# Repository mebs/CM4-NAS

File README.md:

# CM4 NAS Board [UNMAINTAINED]

This Compute Module 4 carrier board design exposes a subset of the CM4's interfaces, including its single PCIe 2.0 lane to accept an external SATA controller card.
This design is based off of the official Raspberry Pi Foundation's CM4 IO board (the KiCad project is available on the [IO board official page](https://www.raspberrypi.org/products/compute-module-4-io-board/?resellerType=home)). Removed the IO that was less relevant for a NAS and rearranged the remaining interfaces for a smaller footprint that would fit within the width of a standard 3.5" hard drive.

The board was intentionally kept simple to limit mistakes as this is my first ever attempt at designing a PCB and I have no background in electronics, so all the power management is left to external power supplies and buck converters. It's important to use good quality regulated power supplies with this board as it offers no protection other than what is built into the CM4.

Also made 3D printed enclosure for the final product. Design available here: https://www.thingiverse.com/thing:4820662

Feel free to explore the discussion section of this repo to share ideas.

[Latest Reddit post here.](https://www.reddit.com/r/raspberry_pi/comments/mkbxss/cm4_custom_nas_complete/)

##### Table of Contents
- [Software](#software)
- [Board IO](#board-io)
  * [CM4 IO Breakout](#cm4-io-breakout)
  * [Other Connections on the Board](#other-connections-on-the-board)
- [PCB Assembly](#pcb-assembly)
  * [Manufacturing](#manufacturing)
  * [Required Parts](#required-parts)
  * [Building](#building)
- [Pinout](#pinout)
- [Revision History](#revision-history)

# Software
For the software part of this project, I highly recommend [Jeff Geerling's repo](https://github.com/geerlingguy/raspberry-pi-pcie-devices/issues), where he documented similar endeavors, but you will likely have to recompile the kernel after enabling some modules to be able to use a PCIe SATA controller.

Don't hesitate to ask questions in the Discussion tab of this repo.

# Board IO
## CM4 IO Breakout
The interfaces the board forwards from the CM4 are the following:
- **PCIe x1 Gen2**: Good old PCIe 2.0, nothing special about it... if not that it's on a Raspberry Pi.
- **Ethernet**: To reduce the number of components on the board and make assembly easier, a MagJack is used instead of a simple RJ45 connector. I had to look this up when I saw it in the IO board design, but a MagJack seems to be simply an RJ45 connector with integrated filters to help with signal integrity. Footprint is specific to the part listed bellow.
- **Single master/slave USB, selected with jumper**: A USB type A port to plug a keyboard, a flash drive, a hub, or whatever you want to use as a USB slave to the CM4. Footprint is not standard so make sure it fits yours if you manufacture the PCB. Can also be used in slave mode (CM4 as slave). You would use this to program the eMMC with you computer. This connection taps into the same single USB bus the CM4 has to offer, but when this is used, the VCC input from the master signals that the CM4 should behave as a slave. Currently the footprint for this is a simple 5 pin header.
- **Full size HDMI**:  Mostly for debugging purposes, hooked to the HDMI0 output of the CM4.
- **I²C**: This is marked "OLED" on the board because this was the intended use, but you can use this to slave any I²C device to the CM4. Five-pin JST connector footprint (fits simple headers too).
- **Single wire temperature sensor**: Marked "Temp_sensor" on the board, hooked to GPIO_4 on the CM4. I would recommend using it for a temp sensor near the SATA controller because they can get really hot and control the fan (see bellow) based on that.
- **9 GPIOs**: General purpose IO header, including Gnd, 3V3 and 5V pins.
- **Configuration headers**: nRPIBOOT, EEPROM_nWP, AIN1, SYNC_IN, SYNC_OUT, TV_OUT, GLOBAL_EN, RUN_PG, WL_nDis, BT_nDis. The pinout is detailed on the board.

## Other Connections on the Board
Other than relaying the compute module's IOs, the board adds other connections, mainly for power.
- **Fan control**: The board expects a dedicated PWM fan controller IC (see part list). Its output is routed to this JST connector (or your typical PWM fan connector) marked "Fan_PWM" on the board.
- **USB selection headers**: To avoid needing a USB MUX on board, this header should be used with a jumper to select if you want to use the USB bus as master or as slave.
- **Power input**: The board expects a 5V input for the CM4, and a 12V input for the PCIe card, both through the same JST connector labeled "PWR_IN".
- **3V3 buck**: The PCIe card also requires a dedicated 3V3 supply. This can be provided through the "3V3_BUCK" header near the power input. The pinout was made to accommodate [this daughter board](https://www.aliexpress.com/item/32817933017.html?spm=a2g0s.9042311.0.0.27424c4dr779wi) from AliExpress, but you can use whatever you want for as long as you follow the pinout bellow.
- **HDDs power**: Labeled "SATA_PWR". This is the power rail for the hard drives.

# PCB Assembly
## Manufacturing
There is a *Fab* folder at the repo's root. This folder contains all the files that you need to order PCBs from a manufacturer. You will find in the folder a Fab_rev1.4.zip archive that is all you need to order from JLC PCB. This is the latest version and the one I have been running for months now.

## Required Parts
Other than the standard caps and resistors, here are the components you will need if you want to assemble the board:
- **High density connectors** ([digikey](https://www.digikey.ca/en/products/detail/hirose-electric-co-ltd/DF40C-100DS-0.4V%2851%29/1969495), [LCSC](https://lcsc.com/product-detail/Mezzanine-Connectors-Board-to-Board_HRS-Hirose-DF40C-100DS-0-4V-51_C597931.html)): You will need these to connect the CM4 to the board. They can be very daunting, but I found [this video](https://www.youtube.com/watch?v=eukcrFc18P4) of someone neatly soldering them with a hot air gun. When I finaly got to try it, I was surprise at how doable it was.
- **MagJack** ([digikey](https://www.digikey.ca/en/products/detail/bel-fuse-inc/0826-1G1T-43-F/2107992)): I made the footprint for this specific one. It's expensive and I should have looked on LCSC before ordering.
- **Fan controller** ([digikey](https://www.digikey.ca/en/products/detail/microchip-technology/EMC2301-1-ACZL-TR/4696431), [LCSC](https://lcsc.com/product-detail/_MICROCHIP_EMC2301-1-ACZL-TR_EMC2301-1-ACZL-TR_C148036.html)): This chip is the exact same one that is on the official IO board and it's controlled by the CM4 through I²C.
- **ESD sinks** ([digikey](https://www.digikey.ca/en/products/detail/texas-instruments/TPD4EUSB30DQAR/2503671), [LCSC](https://lcsc.com/product-detail/Diodes-ESD_Texas-Instruments-TPD4EUSB30DQAR_C90627.html)): They are optional in my (very uninformed) opinion. I think they were included on the IO board for POE applications mostly.
- **Signal buffer** ([digikey](https://www.digikey.ca/en/products/detail/diodes-incorporated/74LVC1G07SE-7/2356550), [LCSC](https://lcsc.com/product-detail/Logic-Buffers-Drivers-Receivers-Transceivers_Diodes-Incorporated-74LVC1G07SE-7_C67531.html)): Used for the power LED and to buffer RUN_PG signal to be able to wake the CM4 from a sleep state.
- **HDMI connector** ([LCSC](https://lcsc.com/product-detail/Audio-Video-Connectors_SOFNG-HDMI-019S_C111617.html)): Basic full size HDMI connector.

## Building
To build the board, you will need a soldering iron and a hot air gun (or a reflow oven). I would recommend starting with the Hirose high density connectors as they are without a doubt the hardest part. [This video](https://www.youtube.com/watch?v=eukcrFc18P4) I referred to earlier is a good starting point, it makes for a fine tutorial.
It only took a couple tries before I could get a decent result (image from microscope at around 50-60x):

Once the HD connectors are in place, you can move on to the ESD sinks. They are very small and can also be daunting, but soldering them turned out to be easier than expected.
The trick is to put as little solder paste as possible and the chips will naturally be pulled in place by the solder's surface tension.

The rest of the parts should be fairly easy to solder with a standard iron.

# Pinout

# Revision History
- **1**: Initial version
- **1.1**: Fixed wrong footprint for fan controller
- **1.2**: Changed the USB select headers for a simpler solution with a single jumper
- **1.3**: Replaced the HDMI header by a full size HDMI female connector, exposed 9 GPIOs, inverted polarity back for PCIe Tx/Rx signals and added a power LED.
- **1.4**: Add pin to OLED connector for button, use SMD caps and LEDs, more info on silkscreen and fixed some traces.

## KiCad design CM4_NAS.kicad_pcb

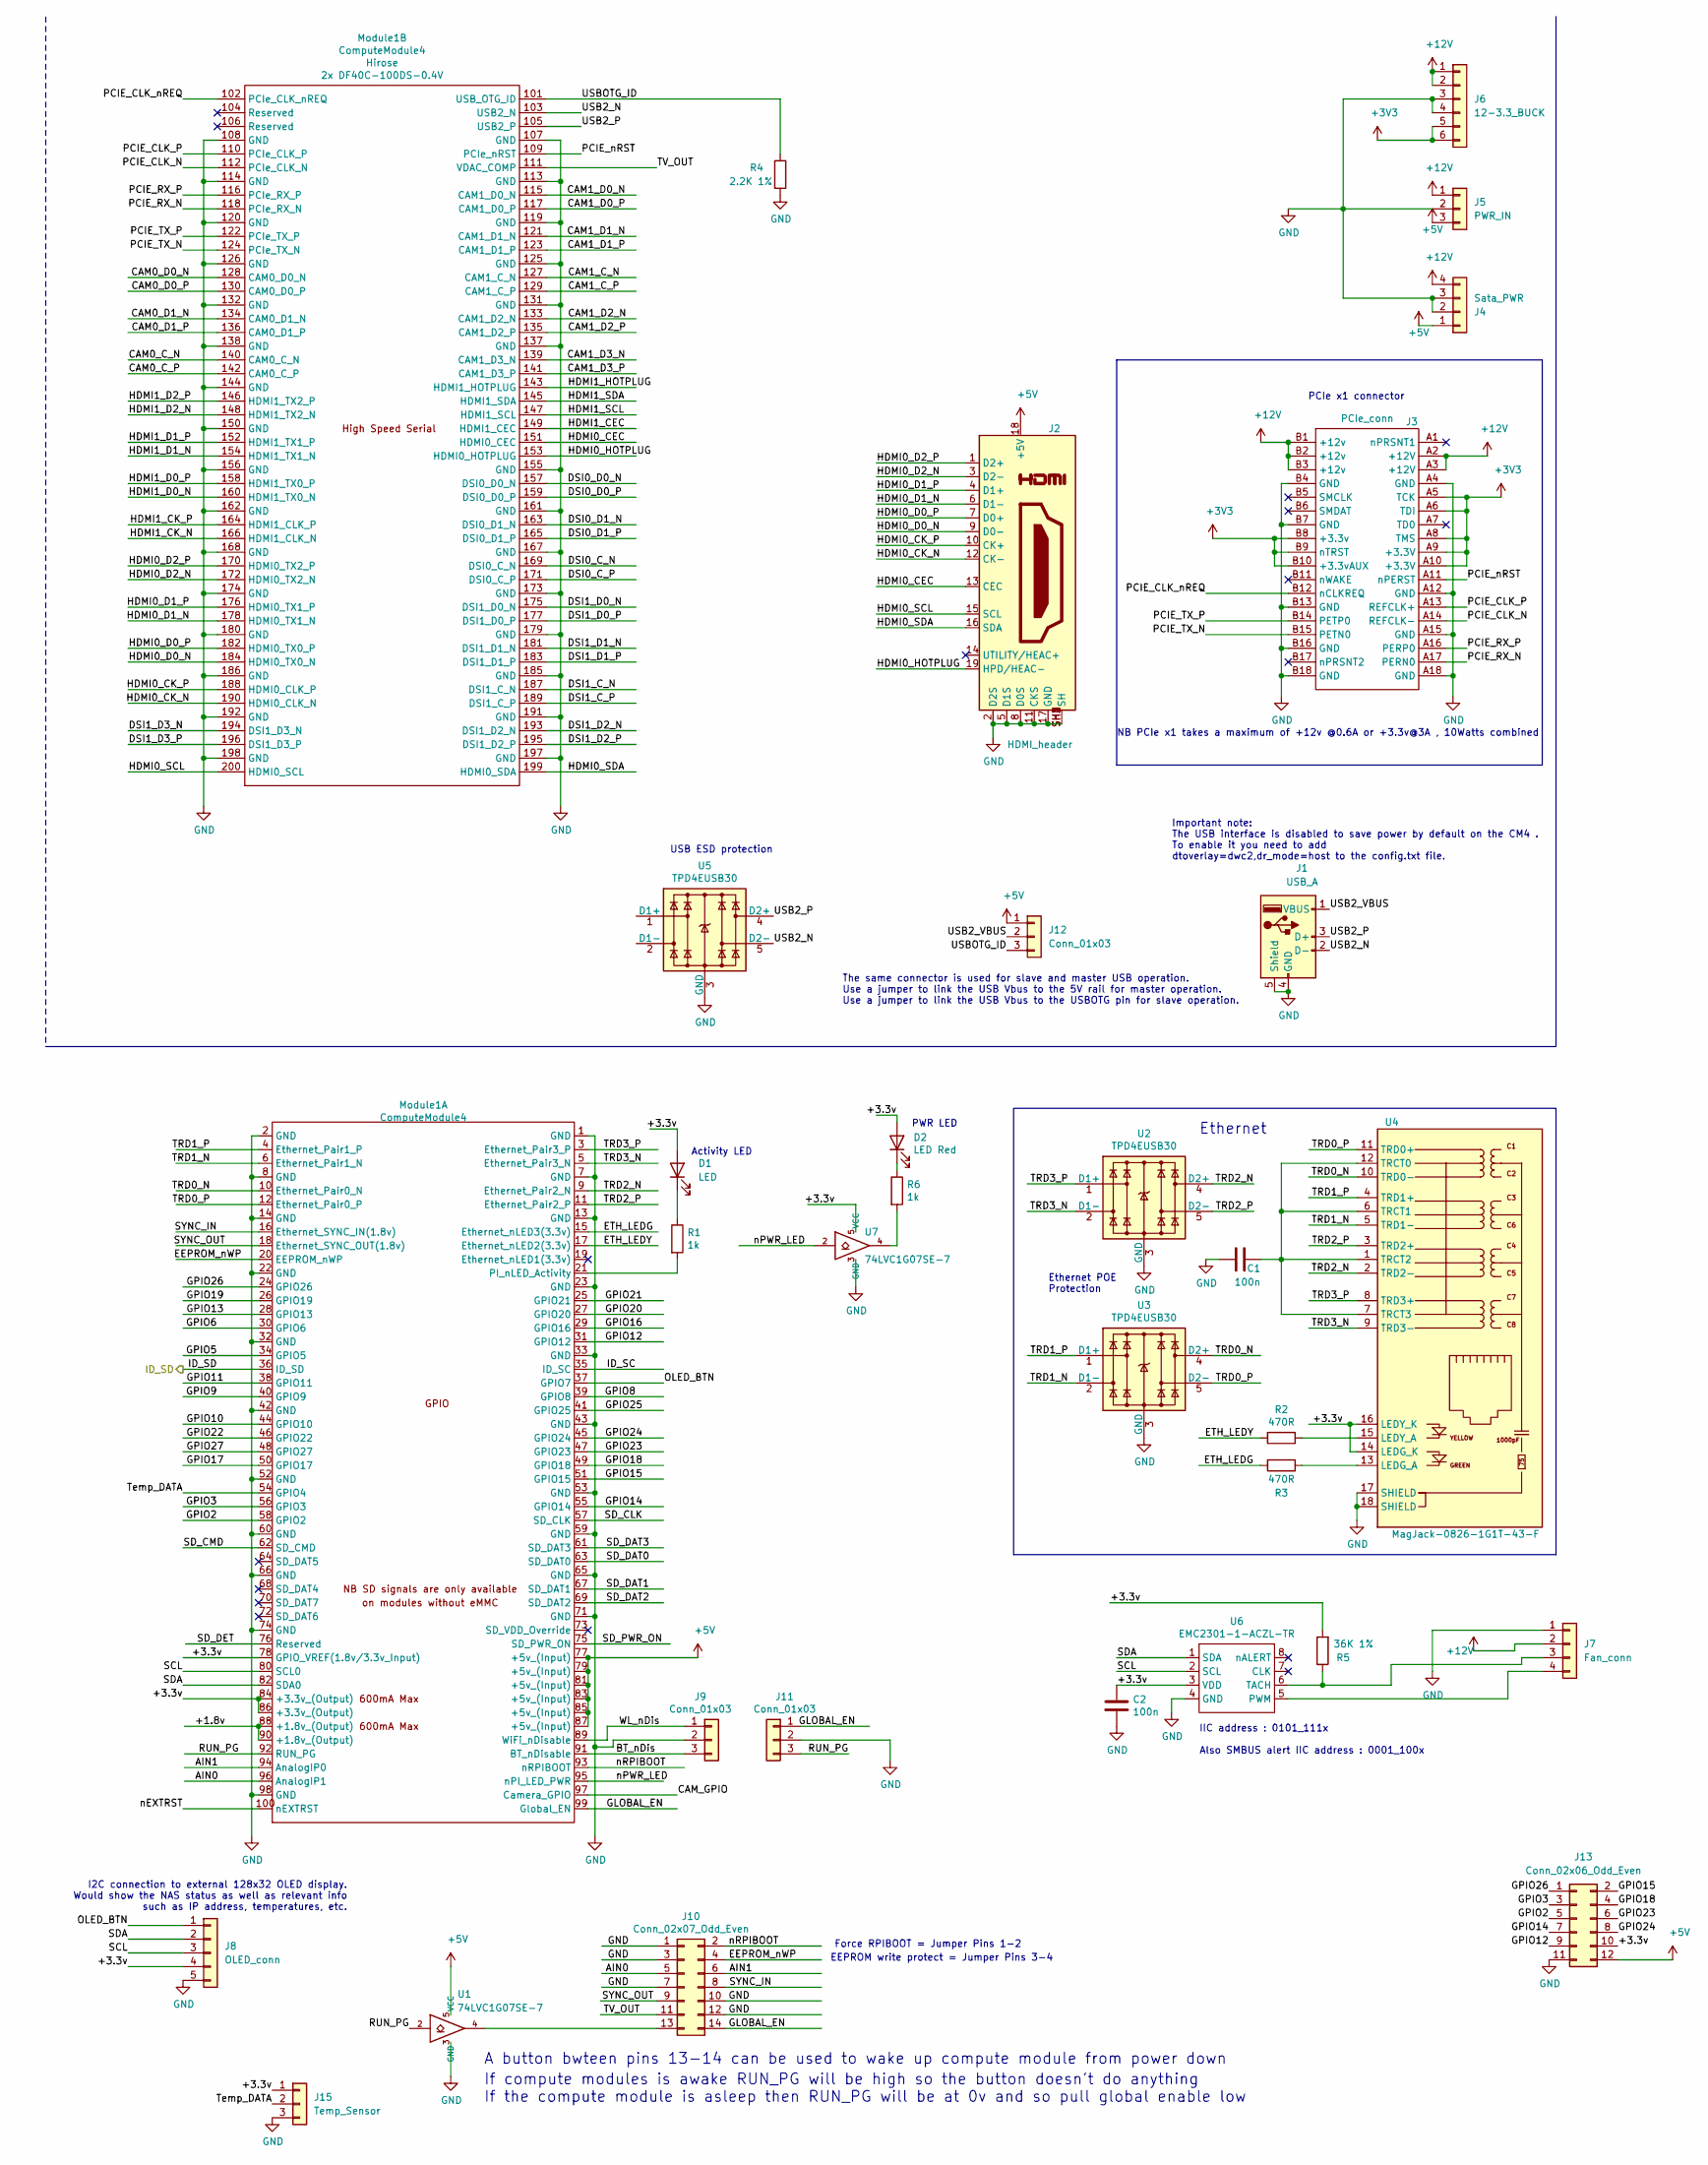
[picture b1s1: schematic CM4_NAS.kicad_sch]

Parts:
C1, C2: 100n; C_0805_2012Metric_Pad1.18x1.45mm_HandSolder
D1: LED; LED_0805_2012Metric_Pad1.15x1.40mm_HandSolder
D2: LED Red; LED_0805_2012Metric_Pad1.15x1.40mm_HandSolder
J1: USB_A; USB_A_Vertical
J2: HDMI_header; HDMI EDAC 690-019-298-412
J3: PCIe_conn; PCIex1-36; Part Description PCI Express/PCI Connectors PCIE THROUGH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
J4: Sata_PWR; JST_XH_B4B-XH-A_1x04_P2.50mm_Vertical
J5: PWR_IN; JST_XH_B3B-XH-A_1x03_P2.50mm_Vertical
J6: 12-3.3_BUCK; PinSocket_1x06_P2.54mm_Vertical
J7: Fan_conn; JST_XH_B4B-XH-A_1x04_P2.50mm_Vertical
J8: OLED_conn; JST_XH_B5B-XH-A_1x05_P2.50mm_Vertical
J9, J11: Conn_01x03; PinHeader_1x03_P2.54mm_Vertical; Part Description 3pin 0.1" connector
J10: Conn_02x07_Odd_Even; PinHeader_2x07_P2.54mm_Vertical; Part Description PinHeader_2x07_P2.54mm_Vertical
J12: Conn_01x03; PinHeader_1x03_P2.54mm_Vertical
J13: Conn_02x06_Odd_Even; PinHeader_2x06_P2.54mm_Vertical
J15: Temp_Sensor; PinSocket_1x03_P2.54mm_Vertical
Module1: ComputeModule4; Raspberry-Pi-4-Compute-Module; Part Description 100 Position Connector Receptacle, Cent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
R1, R6: 1k; R_Axial_DIN0207_L6.3mm_D2.5mm_P7.62mm_Horizontal; Part Description Resistor 1K M1005 1% 63mW
R2: 470R; R_Axial_DIN0207_L6.3mm_D2.5mm_P7.62mm_Horizontal
R3: 470R; R_Axial_DIN0207_L6.3mm_D2.5mm_P7.62mm_Horizontal; Part Description Resistor 470R M1005 1% 63mW
R4: 2.2K 1%; R_Axial_DIN0207_L6.3mm_D2.5mm_P7.62mm_Horizontal
R5: 36K 1%; R_Axial_DIN0207_L6.3mm_D2.5mm_P7.62mm_Horizontal
U1, U7: 74LVC1G07SE-7; SOT-353_SC-70-5; Part Description Buffer, Non-Inverting 1 Element 1 Bit p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
U2, U3, U5: TPD4EUSB30; USON-10_2.5x1.0mm_P0.5mm; Part Description Quad TVS diode for high speed signals (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
U4: MagJack-0826-1G1T-43-F; MagJack_0826-1G1T-43-F
U6: EMC2301-1-ACZL-TR; MSOP-8_3x3mm_P0.65mm; Part Description Motor Driver PWM 8-MSOP

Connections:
+3V3: J3.A5 (TCK), J3.A6 (TDI), J3.A8 (TMS), J3.A9 (+3.3V), J3.A10 (+3.3V), J3.B8 (+3.3v), J3.B9 (nTRST), J3.B10 (+3.3vAUX), J6.5, J6.6
+5V: J2.18 (+5V), J4.1, J5.3, J12.1, J13.12, Module1.77 (+5v_(Input)), Module1.79 (+5v_(Input)), Module1.81 (+5v_(Input)), Module1.83 (+5v_(Input)), Module1.85 (+5v_(Input)), Module1.87 (+5v_(Input)), U1.5 (VCC)
+12V: J3.A2 (+12V), J3.A3 (+12V), J3.B1 (+12v), J3.B2 (+12v), J3.B3 (+12v), J4.4, J5.1, J6.1, J6.2, J7.2
/+1.8v: Module1.88 (+1.8v_(Output)), Module1.90 (+1.8v_(Output))
/+3.3v: C2.1, D1.2 (A), D2.2 (A), J8.4, J13.10, J15.1, Module1.78 (GPIO_VREF(1.8v/3.3v_Input)), Module1.84 (+3.3v_(Output)), Module1.86 (+3.3v_(Output)), R5.2, U4.14 (LEDG_K), U4.16 (LEDY_K), U6.3 (VDD), U7.5 (VCC)
/AIN0: J10.5, Module1.96 (AnalogIP1)
/AIN1: J10.6, Module1.94 (AnalogIP0)
/BT_nDis: J9.3, Module1.91 (BT_nDisable)
/CAM0_C_N: Module1.140 (CAM0_C_N)
/CAM0_C_P: Module1.142 (CAM0_C_P)
/CAM0_D0_N: Module1.128 (CAM0_D0_N)
/CAM0_D0_P: Module1.130 (CAM0_D0_P)
/CAM0_D1_N: Module1.134 (CAM0_D1_N)
/CAM0_D1_P: Module1.136 (CAM0_D1_P)
/CAM1_C_N: Module1.127 (CAM1_C_N)
/CAM1_C_P: Module1.129 (CAM1_C_P)
/CAM1_D0_N: Module1.115 (CAM1_D0_N)
/CAM1_D0_P: Module1.117 (CAM1_D0_P)
/CAM1_D1_N: Module1.121 (CAM1_D1_N)
/CAM1_D1_P: Module1.123 (CAM1_D1_P)
/CAM1_D2_N: Module1.133 (CAM1_D2_N)
/CAM1_D2_P: Module1.135 (CAM1_D2_P)
/CAM1_D3_N: Module1.139 (CAM1_D3_N)
/CAM1_D3_P: Module1.141 (CAM1_D3_P)
/CAM_GPIO: Module1.97 (Camera_GPIO)
/DSI0_C_N: Module1.169 (DSI0_C_N)
/DSI0_C_P: Module1.171 (DSI0_C_P)
/DSI0_D0_N: Module1.157 (DSI0_D0_N)
/DSI0_D0_P: Module1.159 (DSI0_D0_P)
/DSI0_D1_N: Module1.163 (DSI0_D1_N)
/DSI0_D1_P: Module1.165 (DSI0_D1_P)
/DSI1_C_N: Module1.187 (DSI1_C_N)
/DSI1_C_P: Module1.189 (DSI1_C_P)
/DSI1_D0_N: Module1.175 (DSI1_D0_N)
/DSI1_D0_P: Module1.177 (DSI1_D0_P)
/DSI1_D1_N: Module1.181 (DSI1_D1_N)
/DSI1_D1_P: Module1.183 (DSI1_D1_P)
/DSI1_D2_N: Module1.193 (DSI1_D2_N)
/DSI1_D2_P: Module1.195 (DSI1_D2_P)
/DSI1_D3_N: Module1.194 (DSI1_D3_N)
/DSI1_D3_P: Module1.196 (DSI1_D3_P)
/EEPROM_nWP: J10.4, Module1.20 (EEPROM_nWP)
/ETH_LEDG: Module1.15 (Ethernet_nLED3(3.3v)), R3.2
/ETH_LEDY: Module1.17 (Ethernet_nLED2(3.3v)), R2.2
/GLOBAL_EN: J10.14, J11.1, Module1.99 (Global_EN)
/GPIO2: J13.5, Module1.58 (GPIO2)
/GPIO3: J13.3, Module1.56 (GPIO3)
/GPIO5: Module1.34 (GPIO5)
/GPIO6: Module1.30 (GPIO6)
/GPIO8: Module1.39 (GPIO8)
/GPIO9: Module1.40 (GPIO9)
/GPIO10: Module1.44 (GPIO10)
/GPIO11: Module1.38 (GPIO11)
/GPIO12: J13.9, Module1.31 (GPIO12)
/GPIO13: Module1.28 (GPIO13)
/GPIO14: J13.7, Module1.55 (GPIO14)
/GPIO15: J13.2, Module1.51 (GPIO15)
/GPIO16: Module1.29 (GPIO16)
/GPIO17: Module1.50 (GPIO17)
/GPIO18: J13.4, Module1.49 (GPIO18)
/GPIO19: Module1.26 (GPIO19)
/GPIO20: Module1.27 (GPIO20)
/GPIO21: Module1.25 (GPIO21)
/GPIO22: Module1.46 (GPIO22)
/GPIO23: J13.6, Module1.47 (GPIO23)
/GPIO24: J13.8, Module1.45 (GPIO24)
/GPIO25: Module1.41 (GPIO25)
/GPIO26: J13.1, Module1.24 (GPIO26)
/GPIO27: Module1.48 (GPIO27)
/HDMI0_CEC: J2.13 (CEC), Module1.151 (HDMI0_CEC)
/HDMI0_CK_N: J2.12 (CK-), Module1.190 (HDMI0_CLK_N)
/HDMI0_CK_P: J2.10 (CK+), Module1.188 (HDMI0_CLK_P)
/HDMI0_D0_N: J2.9 (D0-), Module1.184 (HDMI0_TX0_N)
/HDMI0_D0_P: J2.7 (D0+), Module1.182 (HDMI0_TX0_P)
/HDMI0_D1_N: J2.6 (D1-), Module1.178 (HDMI0_TX1_N)
/HDMI0_D1_P: J2.4 (D1+), Module1.176 (HDMI0_TX1_P)
/HDMI0_D2_N: J2.3 (D2-), Module1.172 (HDMI0_TX2_N)
/HDMI0_D2_P: J2.1 (D2+), Module1.170 (HDMI0_TX2_P)
/HDMI0_HOTPLUG: J2.19 (HPD/HEAC-), Module1.153 (HDMI0_HOTPLUG)
/HDMI0_SCL: J2.15 (SCL), Module1.200 (HDMI0_SCL)
/HDMI0_SDA: J2.16 (SDA), Module1.199 (HDMI0_SDA)
/HDMI1_CEC: Module1.149 (HDMI1_CEC)
/HDMI1_CK_N: Module1.166 (HDMI1_CLK_N)
/HDMI1_CK_P: Module1.164 (HDMI1_CLK_P)
/HDMI1_D0_N: Module1.160 (HDMI1_TX0_N)
/HDMI1_D0_P: Module1.158 (HDMI1_TX0_P)
/HDMI1_D1_N: Module1.154 (HDMI1_TX1_N)
/HDMI1_D1_P: Module1.152 (HDMI1_TX1_P)
/HDMI1_D2_N: Module1.148 (HDMI1_TX2_N)
/HDMI1_D2_P: Module1.146 (HDMI1_TX2_P)
/HDMI1_HOTPLUG: Module1.143 (HDMI1_HOTPLUG)
/HDMI1_SCL: Module1.147 (HDMI1_SCL)
/HDMI1_SDA: Module1.145 (HDMI1_SDA)
/ID_SC: Module1.35 (ID_SC)
/ID_SD: Module1.36 (ID_SD)
/OLED_BTN: J8.1, Module1.37 (GPIO7)
/PCIE_CLK_N: J3.A14 (REFCLK-), Module1.112 (PCIe_CLK_N)
/PCIE_CLK_P: J3.A13 (REFCLK+), Module1.110 (PCIe_CLK_P)
/PCIE_CLK_nREQ: J3.B12 (nCLKREQ), Module1.102 (PCIe_CLK_nREQ)
/PCIE_RX_N: J3.A17 (PERN0), Module1.118 (PCIe_RX_N)
/PCIE_RX_P: J3.A16 (PERP0), Module1.116 (PCIe_RX_P)
/PCIE_TX_N: J3.B15 (PETN0), Module1.124 (PCIe_TX_N)
/PCIE_TX_P: J3.B14 (PETP0), Module1.122 (PCIe_TX_P)
/PCIE_nRST: J3.A11 (nPERST), Module1.109 (PCIe_nRST)
/RUN_PG: J11.3, Module1.92 (RUN_PG), U1.2
/SCL: J8.3, Module1.80 (SCL0), U6.2 (SCL)
/SDA: J8.2, Module1.82 (SDA0), U6.1 (SDA)
/SD_CLK: Module1.57 (SD_CLK)
/SD_CMD: Module1.62 (SD_CMD)
/SD_DAT0: Module1.63 (SD_DAT0)
/SD_DAT1: Module1.67 (SD_DAT1)
/SD_DAT2: Module1.69 (SD_DAT2)
/SD_DAT3: Module1.61 (SD_DAT3)
/SD_DET: Module1.76 (Reserved)
/SD_PWR_ON: Module1.75 (SD_PWR_ON)
/SYNC_IN: J10.8, Module1.16 (Ethernet_SYNC_IN(1.8v))
/SYNC_OUT: J10.9, Module1.18 (Ethernet_SYNC_OUT(1.8v))
/TRD0_N: Module1.10 (Ethernet_Pair0_N), U3.4 (D2+), U3.7, U4.10 (TRD0-)
/TRD0_P: Module1.12 (Ethernet_Pair0_P), U3.5 (D2-), U3.6, U4.11 (TRD0+)
/TRD1_N: Module1.6 (Ethernet_Pair1_N), U3.2 (D1-), U3.9, U4.5 (TRD1-)
/TRD1_P: Module1.4 (Ethernet_Pair1_P), U3.1 (D1+), U3.10, U4.4 (TRD1+)
/TRD2_N: Module1.9 (Ethernet_Pair2_N), U2.4 (D2+), U2.7, U4.2 (TRD2-)
/TRD2_P: Module1.11 (Ethernet_Pair2_P), U2.5 (D2-), U2.6, U4.3 (TRD2+)
/TRD3_N: Module1.5 (Ethernet_Pair3_N), U2.2 (D1-), U2.9, U4.9 (TRD3-)
/TRD3_P: Module1.3 (Ethernet_Pair3_P), U2.1 (D1+), U2.10, U4.8 (TRD3+)
/TV_OUT: J10.11, Module1.111 (VDAC_COMP)
/Temp_DATA: J15.2, Module1.54 (GPIO4)
/USB2_N: J1.2 (D-), Module1.103 (USB2_N), U5.5 (D2-), U5.6
/USB2_P: J1.3 (D+), Module1.105 (USB2_P), U5.4 (D2+), U5.7
/USB2_VBUS: J1.1 (VBUS), J12.2
/USBOTG_ID: J12.3, Module1.101 (USB_OTG_ID), R4.1
/WL_nDis: J9.1, Module1.89 (WiFi_nDisable)
/nEXTRST: Module1.100 (nEXTRST)
/nPWR_LED: Module1.95 (nPI_LED_PWR), U7.2
/nRPIBOOT: J10.2, Module1.93 (nRPIBOOT)
GND: C1.2, C2.2, J1.4 (GND), J1.5 (Shield), J2.2 (D2S), J2.5 (D1S), J2.8 (D0S), J2.11 (CKS), J2.17 (GND), J2.SH1 (SH), J2.SH2 (SH), J2.SH3 (SH), J2.SH4 (SH), J3.A4 (GND), J3.A12 (GND), J3.A15 (GND), J3.A18 (GND), J3.B4 (GND), J3.B7 (GND), J3.B13 (GND), J3.B16 (GND), J3.B18 (GND), J4.2, J4.3, J5.2, J6.3, J6.4, J7.1, J8.5, J9.2, J10.1, J10.3, J10.7, J10.10, J10.12, J11.2, J13.11, J15.3, Module1.1 (GND), Module1.2 (GND), Module1.7 (GND), Module1.8 (GND), Module1.13 (GND), Module1.14 (GND), Module1.22 (GND), Module1.23 (GND), Module1.32 (GND), Module1.33 (GND), Module1.42 (GND), Module1.43 (GND), Module1.52 (GND), Module1.53 (GND), Module1.59 (GND), Module1.60 (GND), Module1.65 (GND), Module1.66 (GND), Module1.71 (GND), Module1.74 (GND), Module1.98 (GND), Module1.107 (GND), Module1.108 (GND), Module1.113 (GND), Module1.114 (GND), Module1.119 (GND), Module1.120 (GND), Module1.125 (GND), Module1.126 (GND), Module1.131 (GND), Module1.132 (GND), Module1.137 (GND), Module1.138 (GND), Module1.144 (GND), Module1.150 (GND), Module1.155 (GND), Module1.156 (GND), Module1.161 (GND), Module1.162 (GND), Module1.167 (GND), Module1.168 (GND), Module1.173 (GND), Module1.174 (GND), Module1.179 (GND), Module1.180 (GND), Module1.185 (GND), Module1.186 (GND), Module1.191 (GND), Module1.192 (GND), Module1.197 (GND), Module1.198 (GND), R4.2, U1.3 (GND), U2.3 (GND), U2.8 (GND), U3.3 (GND), U3.8 (GND), U4.17 (SHIELD), U4.18 (SHIELD), U5.3 (GND), U5.8 (GND), U6.4 (GND), U7.3 (GND)
unnamed: C1.1, U4.1 (TRCT2), U4.6 (TRCT1), U4.7 (TRCT3), U4.12 (TRCT0)
unnamed: D1.1 (K), R1.1
unnamed: D2.1 (K), R6.1
unnamed: J7.3, R5.1, U6.6 (TACH)
unnamed: J7.4, U6.5 (PWM)
unnamed: J10.13, U1.4
unnamed: Module1.21 (PI_nLED_Activity), R1.2
unnamed: R2.1, U4.15 (LEDY_A)
unnamed: R3.1, U4.13 (LEDG_A)
unnamed: R6.2, U7.4
unnamed: U5.1 (D1+), U5.10
unnamed: U5.2 (D1-), U5.9

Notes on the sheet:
I2C connection to external 128x32 OLED display. Would show the NAS status as well as relevant info such as IP address, temperatures, etc.
A button bwteen pins 13-14 can be used to wake up compute module from power down
If compute modules is awake RUN_PG will be high so the button doesn't do anything If the compute module is asleep then RUN_PG will be at 0v and so pull global enable low
Activity LED
USB ESD protection
The same connector is used for slave and master USB operation. Use a jumper to link the USB Vbus to the 5V rail for master operation. Use a jumper to link the USB Vbus to the USBOTG pin for slave operation.
PWR LED
Force RPIBOOT = Jumper Pins 1-2
Ethernet POE Protection
EEPROM write protect = Jumper Pins 3-4
NB PCIe x1 takes a maximum of +12v @0.6A or +3.3v@3A , 10Watts combined
Important note: The USB interface is disabled to save power by default on the CM4 . To enable it you need to add dtoverlay=dwc2,dr_mode=host to the config.txt file.
Ethernet
IIC address : 0101_111x
Also SMBUS alert IIC address : 0001_100x
PCIe x1 connector

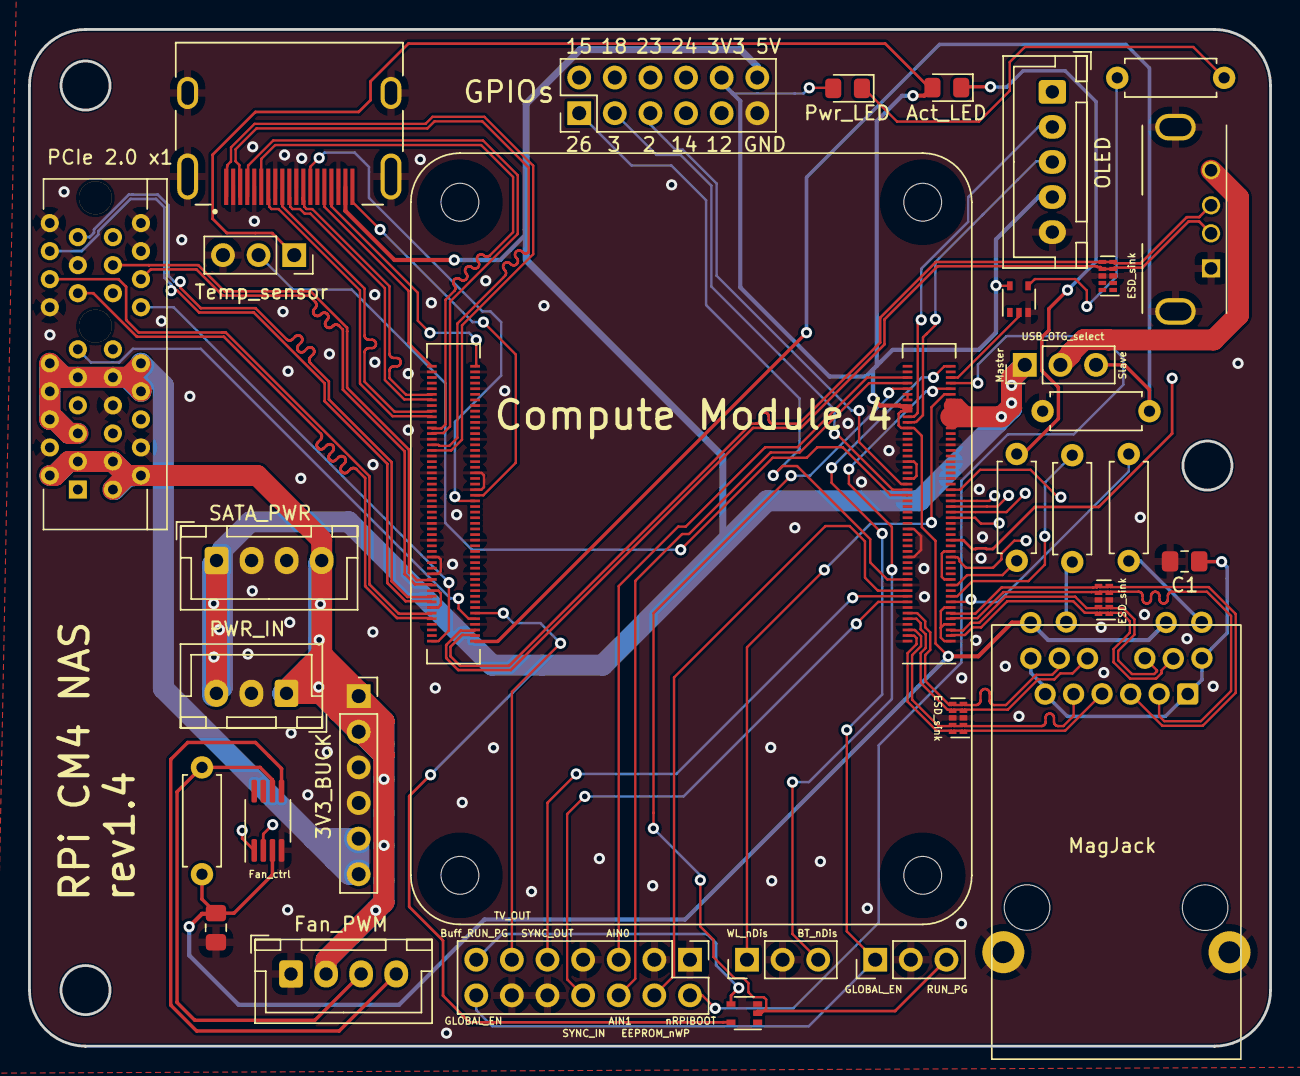
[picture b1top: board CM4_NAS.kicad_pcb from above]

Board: 4 copper layers, 88.5 x 72.5 mm, 32 parts (0 on the bottom side), 77 nets.

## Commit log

2020-12-25 Fixed wrong footprint
2020-12-25 Updated revision on silkscreen
2020-12-26 new usb select header
2020-12-27 HDMI, silkscreen, gpios...
2020-12-28 rev1.4 Add pin to OLED connector for button, use SMD caps and LEDs, more info on silkscreen and fixed some traces.
2021-02-17 New picture
2021-02-21 Link to reddit updated
2021-02-21 Better wordings, typos, updated info
2021-04-07 Link to Thingiverse
2021-04-11 adding BOM file
